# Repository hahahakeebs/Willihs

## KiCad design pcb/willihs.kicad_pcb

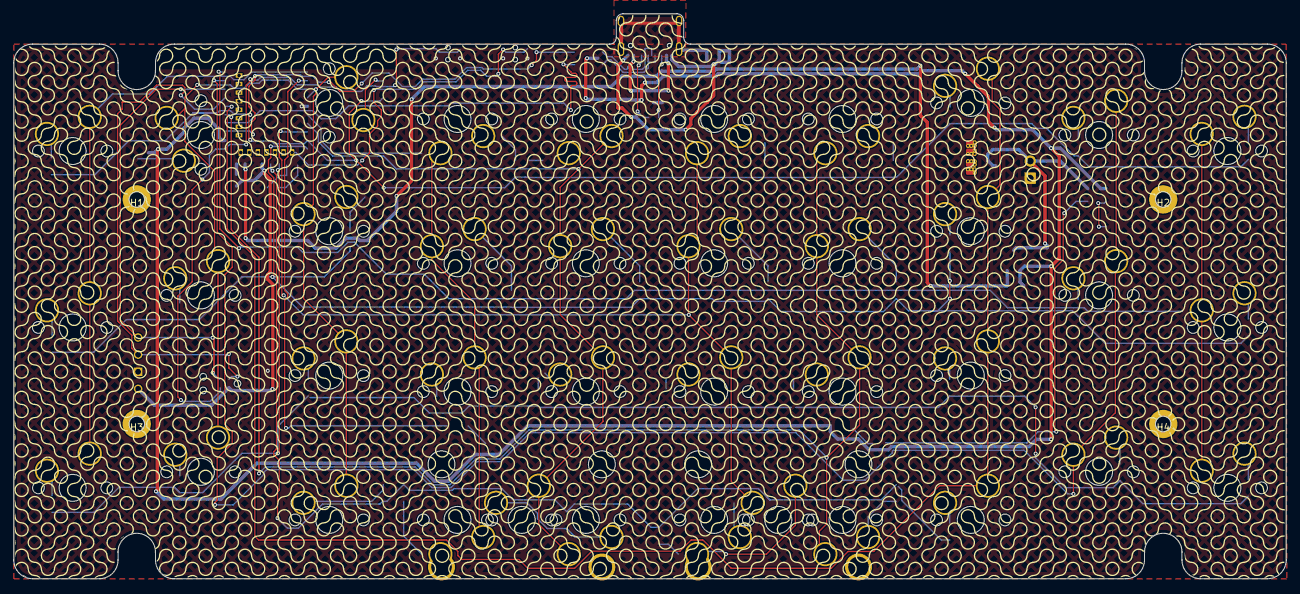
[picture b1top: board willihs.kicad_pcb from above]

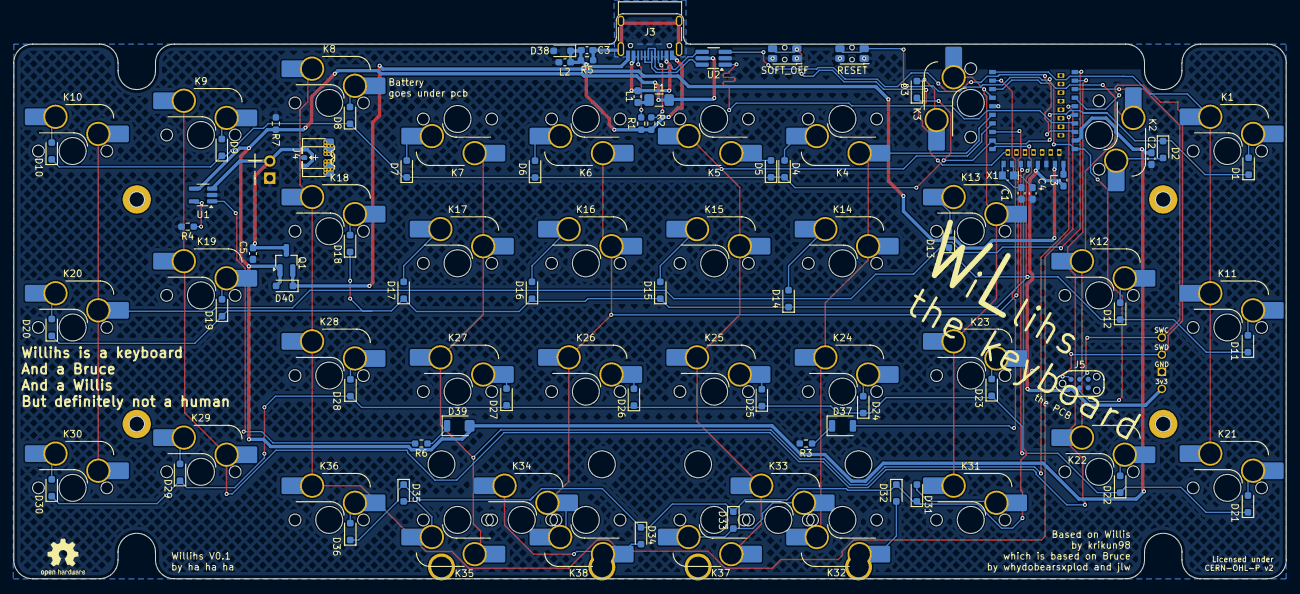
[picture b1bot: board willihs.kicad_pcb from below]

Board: 2 copper layers, 188.9 x 83.9 mm, 112 parts (67 on the bottom side), 77 nets.

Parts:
C1, C4: 12pF; C_0603_1608Metric_Pad1.08x0.95mm_HandSolder
C2, C5: 4.7uF; C_0603_1608Metric_Pad1.08x0.95mm_HandSolder
C3: 100nF; C_0603_1608Metric_Pad1.08x0.95mm_HandSolder
D1, D2, D3, D4, D5, D6, D7, D8, D9, D10, D11, D12, D13, D14, D15, D16, D17, D18, D19, D20, D21, D22, D23, D24, D25, D26, D27, D28, D29, D30, D31, D32, D33, D34, D35, D36: D_Small; D_SOD-323_HandSoldering
D37: BLUE; LED_1206_3216Metric_ReverseMount_Hole1.8x2.4mm
D38: BSD3C051V; D_SOD-323_HandSoldering
D39: RED; LED_1206_3216Metric_ReverseMount_Hole1.8x2.4mm
D40: 1N5819; D_SOD-323_HandSoldering
F1: 500mA; Fuse_1206_3216Metric_Pad1.42x1.75mm_HandSolder
H1, H2, H3, H4: MountingHole; M2_Hole_TH_mod
J1: SWD; connector_swd_REV
J2: Battery; Battery_TH
J3: USB-C Conn; USB_C_Receptacle_HRO_TYPE-C-31-M-12
J4: Pico EZMate; Molex_Pico-EZmate_78171-0002_1x02-1MP_P1.20mm_Vertical reve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
J5: TC2030_SWD; CON_TC2030_outlined
K1, K2, K3, K4, K5, K6, K7, K8, K9, K10, K11, K12, K13, K14, K15, K16, K17, K18, K19, K20, K21, K22, K23, K24, K25, K26, K27, K28, K29, K30, K31, K32, K33, K34, K35, K36, K37, K38: KEYSW; SW_Hotswap_Kailh_MX_Plated_1.00u pinswap no fsilk
L1, L2: HPZ1608U121; L_0603_1608Metric_Pad1.05x0.95mm_HandSolder
L3: 10uH; L_0603_1608Metric_Pad1.05x0.95mm_HandSolder
Q1: AO3407; SOT-23_Handsoldering
R1, R2: 5.1K; R_0603_1608Metric_Pad0.98x0.95mm_HandSolder
R3, R6: 1K; R_0603_1608Metric_Pad0.98x0.95mm_HandSolder
R4: 3K; R_0603_1608Metric_Pad0.98x0.95mm_HandSolder
R5: 1M; R_0603_1608Metric_Pad0.98x0.95mm_HandSolder
R7: 100K; R_0603_1608Metric_Pad0.98x0.95mm_HandSolder
RSW1, RSW2: SW_PUSH; SW_SPST_EVQP7C
S1, S2: Stabilizer; STAB_MX_P_2u
U1: TP4054; SOT-23-5_HandSoldering
U2: USBLC6-2SC6; TSOT-23-6_HandSoldering
U3: E73-2G4M08S1C-52840
X1: 32.768kHz; Crystal_SMD_MicroCrystal_CM9V-T1A-2Pin_1.6x1.0mm_HandSolder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

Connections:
BLUE_LED: D37.2 (A), U3.2 (P1.10)
COL0: K1.1 (A), K11.1 (A), K21.1 (A), U3.1 (P1.11)
COL1: K2.1 (A), K12.1 (A), K22.1 (A), U3.3 (P0.03/AIN1)
COL2: K3.2 (B), K13.2 (B), K23.1 (A), K31.1 (A), U3.4 (P0.28/AIN4)
COL3: K4.1 (A), K14.2 (B), K24.1 (A), K32.2 (B), U3.6 (P1.13)
COL4: K5.2 (B), K15.2 (B), K25.1 (A), K33.1 (A), K37.1 (A), U3.7 (P0.02/AIN0)
COL5: K6.1 (A), K16.2 (B), K26.1 (A), K34.2 (B), K38.2 (B), U3.8 (P0.29/AIN5)
COL6: K7.1 (A), K17.2 (B), K27.1 (A), K35.1 (A), U3.33 (P0.13)
COL7: K8.1 (A), K18.1 (A), K28.1 (A), K36.1 (A), U3.35 (P0.24)
COL8: K9.1 (A), K19.1 (A), K29.2 (B), U3.41 (P0.09/NFC1)
COL9: K10.2 (B), K20.2 (B), K30.2 (B), U3.43 (P0.10/NFC2)
DATA+: U2.1 (I/O1), U3.31 (USB_D+)
DATA-: U2.3 (I/O2), U3.29 (USB_D-)
DCCH: L3.1, U3.25 (DCCH)
GND: C1.1, C2.2, C4.1, C5.2, D38.2 (A2), J1.2, J2.1, J4.1, J5.5 (GND), L2.2, R3.2, R4.2, R7.2, RSW1.1, RSW2.1, U1.2 (VSS), U2.2 (GND), U3.5 (GND), U3.21 (GND), U3.24 (GND)
GNDPWR: C3.1, D38.1 (A1), J3.A1 (GND), J3.A12 (GND), J3.B1 (GND), J3.B12 (GND), L2.1, R1.1, R2.2, R5.2
GNDS: C3.2, J3.S1 (SHIELD), R5.1
unnamed: D1.2 (A), K1.2 (B)
unnamed: D2.2 (A), K2.2 (B)
unnamed: D3.2 (A), K3.1 (A)
unnamed: D4.2 (A), K4.2 (B)
unnamed: D5.2 (A), K5.1 (A)
unnamed: D6.2 (A), K6.2 (B)
unnamed: D7.2 (A), K7.2 (B)
unnamed: D8.2 (A), K8.2 (B)
unnamed: D9.2 (A), K9.2 (B)
unnamed: D10.2 (A), K10.1 (A)
unnamed: D11.2 (A), K11.2 (B)
unnamed: D12.2 (A), K12.2 (B)
unnamed: D13.2 (A), K13.1 (A)
unnamed: D14.2 (A), K14.1 (A)
unnamed: D15.2 (A), K15.1 (A)
unnamed: D16.2 (A), K16.1 (A)
unnamed: D17.2 (A), K17.1 (A)
unnamed: D18.2 (A), K18.2 (B)
unnamed: D19.2 (A), K19.2 (B)
unnamed: D20.2 (A), K20.1 (A)
unnamed: D21.2 (A), K21.2 (B)
unnamed: D22.2 (A), K22.2 (B)
unnamed: D23.2 (A), K23.2 (B)
unnamed: D24.2 (A), K24.2 (B)
unnamed: D25.2 (A), K25.2 (B)
unnamed: D26.2 (A), K26.2 (B)
unnamed: D27.2 (A), K27.2 (B)
unnamed: D28.2 (A), K28.2 (B)
unnamed: D29.2 (A), K29.1 (A)
unnamed: D30.2 (A), K30.1 (A)
unnamed: D31.2 (A), K31.2 (B)
unnamed: D32.2 (A), K32.1 (A)
unnamed: D33.2 (A), K33.2 (B), K37.2 (B)
unnamed: D34.2 (A), K34.1 (A), K38.1 (A)
unnamed: D35.2 (A), K35.2 (B)
unnamed: D36.2 (A), K36.2 (B)
unnamed: D37.1 (K), R3.1
unnamed: D39.1 (K), R6.1
unnamed: F1.1, L1.2
unnamed: J3.A5 (CC1), R2.1
unnamed: J3.B5 (CC2), R1.2
unnamed: J3.A4 (VBUS), J3.A9 (VBUS), J3.B4 (VBUS), J3.B9 (VBUS), L1.1
unnamed: R4.1, U1.5 (PROG)
unnamed: R6.2, U1.1 (STAT)
RESET: J5.3 (~RST), RSW1.2, U3.26 (P0.18/RESET)
ROW0: D1.1 (K), D2.1 (K), D3.1 (K), D4.1 (K), D5.1 (K), D6.1 (K), D7.1 (K), D8.1 (K), D9.1 (K), D10.1 (K), U3.9 (P0.31/AIN7)
ROW1: D11.1 (K), D12.1 (K), D13.1 (K), D14.1 (K), D15.1 (K), D16.1 (K), D17.1 (K), D18.1 (K), D19.1 (K), D20.1 (K), U3.10 (P0.30/AIN6)
ROW2: D21.1 (K), D22.1 (K), D23.1 (K), D24.1 (K), D25.1 (K), D26.1 (K), D27.1 (K), D28.1 (K), D29.1 (K), D30.1 (K), U3.15 (P0.05/AIN3)
ROW3: D31.1 (K), D32.1 (K), D33.1 (K), D34.1 (K), D35.1 (K), D36.1 (K), U3.17 (P1.09)
SOFT_OFF: RSW2.2, U3.12 (P0.26)
SWC: J1.4, J5.4 (SWCLK), U3.39 (SWDCLK)
SWD: J1.3, J5.2 (SWDIO), U3.37 (SWDIO)
USBN: J3.A7 (D-), J3.B7 (D-), U2.4 (I/O2)
USBP: J3.A6 (D+), J3.B6 (D+), U2.6 (I/O1)
VBAT: C5.1, J2.2, J4.2, Q1.3 (D), U1.3 (VBAT)
VBUS: C2.1, D39.2 (A), D40.2 (A), F1.2, Q1.1 (G), R7.1, U1.4 (VDD), U2.5 (VBUS), U3.27 (VBUS)
VDD: J1.1, J5.1 (VCC), L3.2, U3.19 (VDD)
VDDH: D40.1 (K), Q1.2 (S), U3.23 (VDDH)
XL1: C1.2, U3.11 (P0.00/XL1), X1.2
XL2: C4.2, U3.13 (P0.01/XL2), X1.1

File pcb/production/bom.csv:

Designator,Footprint,Quantity,Value,LCSC Part #
"C1, C4",0603,2,12pF,C1642
"C2, C5",0603,2,4.7uF,C19666
C3,0603,1,100nF,C1588
"D1, D10, D11, D12, D13, D14, D15, D16, D17, D18, D19, D2, D20, D21, D22, D23, D24, D25, D26, D27, D28, D29, D3, D30, D31, D32, D33, D34, D35, D36, D4, D5, D6, D7, D8, D9",D_SOD-323_HandSoldering,36,D_Small,C2128
D37,1206,1,BLUE,C375563
D38,D_SOD-323_HandSoldering,1,BSD3C051V,C151996
D39,1206,1,RED, C375561
D40,D_SOD-323_HandSoldering,1,1N5819,C21714236
F1,1206,1,500mA,C883122
"H1, H2, H3, H4",M2_Hole_TH_mod,4,MountingHole,
J1,connector_swd_REV,1,SWD,
J2,Battery_TH,1,Battery,
J3,USB_C_Receptacle_HRO_TYPE-C-31-M-12,1,USB-C Conn,C165948
J4,Molex_Pico-EZmate_78171-0002_1x02-1MP_P1.20mm_Vertical reversible,1,Pico EZMate,
J5,CON_TC2030_outlined,1,TC2030_SWD,
"K1, K10, K11, K12, K13, K14, K15, K16, K17, K18, K19, K2, K20, K21, K22, K23, K24, K25, K26, K27, K28, K29, K3, K30, K31, K32, K33, K34, K35, K36, K37, K38, K4, K5, K6, K7, K8, K9",SW_Hotswap_Kailh_MX_Plated_1.00u pinswap no fsilk,38,KEYSW,
"L1, L2",0603,2,HPZ1608U121,C919153
L3,0603,1,10uH,C275361
Q1,SOT-23_Handsoldering,1,AO3407,C5148473
"R1, R2",0603,2,5.1K,C105580
"R3, R6",0603,2,1K,C22548
R4,0603,1,3K,C4211
R5,0603,1,1M,C22935
R7,0603,1,100K,C14675
"RSW1, RSW2",SW_SPST_EVQP7C,2,SW_PUSH,C388883
"S1, S2",STAB_MX_P_2u,2,Stabilizer,
U1,SOT-23-5_HandSoldering,1,TP4054,C424093
U2,TSOT-23-6_HandSoldering,1,USBLC6-2SC6,C558442
U3,E73-2G4M08S1C-52840,1,E73-2G4M08S1C-52840,C356849
X1,Crystal_SMD_MicroCrystal_CM9V-T1A-2Pin_1.6x1.0mm_HandSoldering,1,32.768kHz,C383846

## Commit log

2025-06-16 first draft of new pcb
2025-06-25 updated pcb and gerbs

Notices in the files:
pcb/willihs.kicad_pcb:
Licensed under
CERN-OHL-P v2
